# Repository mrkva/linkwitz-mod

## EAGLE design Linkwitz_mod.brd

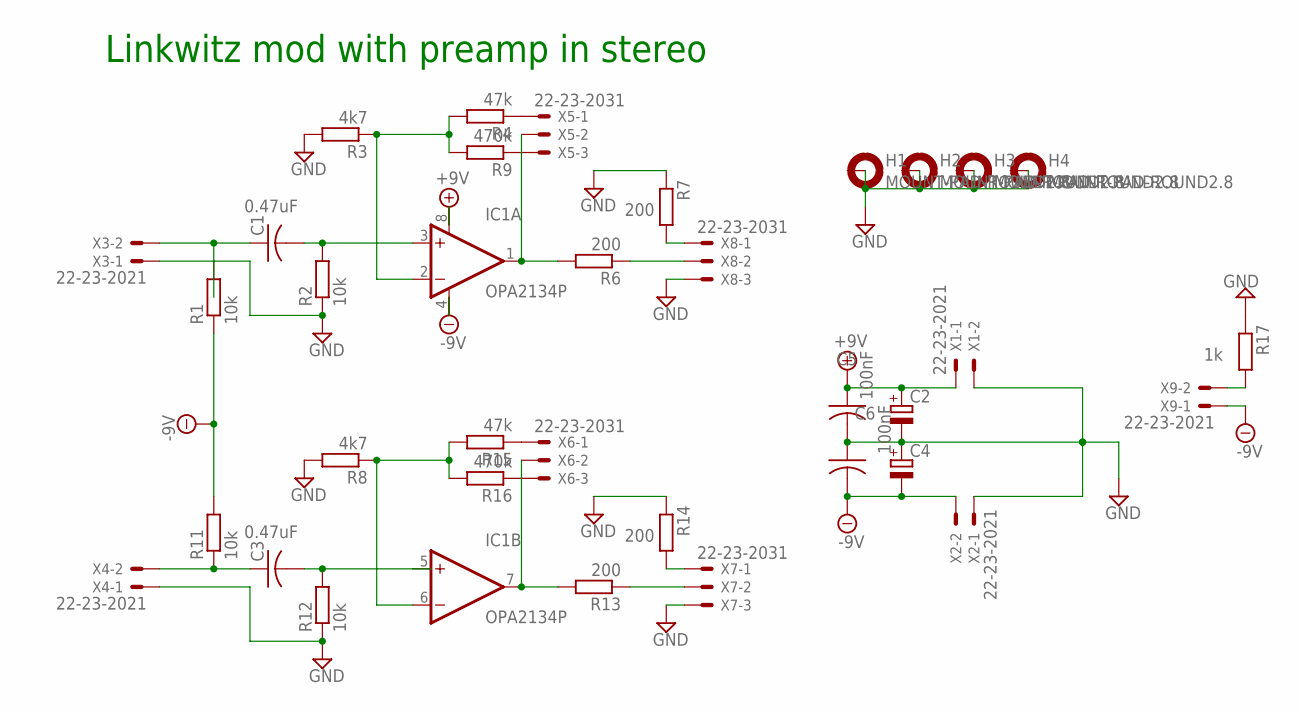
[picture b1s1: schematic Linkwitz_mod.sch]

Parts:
C1, C3: 0.47uF; C050-030X075
C2, C4: CPOL-EUE2,5-6E; E2,5-6E
C5, C6: 100nF; C050-030X075
H1, H2, H3, H4: MOUNT-PAD-ROUND2.8; 2,8-PAD
IC1: OPA2134P; DIL08
R1, R2, R11, R12: 10k; 0309/10
R3, R8: 4k7; 0309/10
R4, R15: 47k; 0309/10
R6, R7, R13, R14: 200; 0309/10
R9, R16: 470k; 0309/10
R17: 1k; 0309/10
X1, X2, X9: 22-23-2021; MPN 22-23-2021
X3, X4: 22-23-2021
X5, X6, X7, X8: 22-23-2031

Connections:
+9V: C2.+, C5.1, IC1.8 (V+), X1.1
-9V: C4.-, C6.2, IC1.4 (V-), R1.1, R11.2, X2.2, X9.1
GND: C2.-, C4.+, C5.2, C6.1, R2.1, R3.2, R7.1, R8.2, R12.1, R14.1, R17.1, X1.2, X2.1, X3.1, X4.1, X7.3, X8.3
unnamed: C1.1, R1.2, X3.2
unnamed: IC1.6 (-IN), R8.1, R15.2, R16.2
unnamed: IC1.2 (-IN), R3.1, R4.2, R9.2
unnamed: C1.2, IC1.3 (+IN), R2.2
unnamed: IC1.1 (OUT), R6.2, X5.2
unnamed: R14.2, X7.1
unnamed: R6.1, X8.2
unnamed: R4.1, X5.1
unnamed: R9.1, X5.3
unnamed: IC1.7 (OUT), R13.2, X6.2
unnamed: R7.2, X8.1
unnamed: C3.1, R11.1, X4.2
unnamed: C3.2, IC1.5 (+IN), R12.2
unnamed: R13.1, X7.2
unnamed: R15.1, X6.1
unnamed: R16.1, X6.3
unnamed: R17.2, X9.2

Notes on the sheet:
Linkwitz mod with preamp in stereo

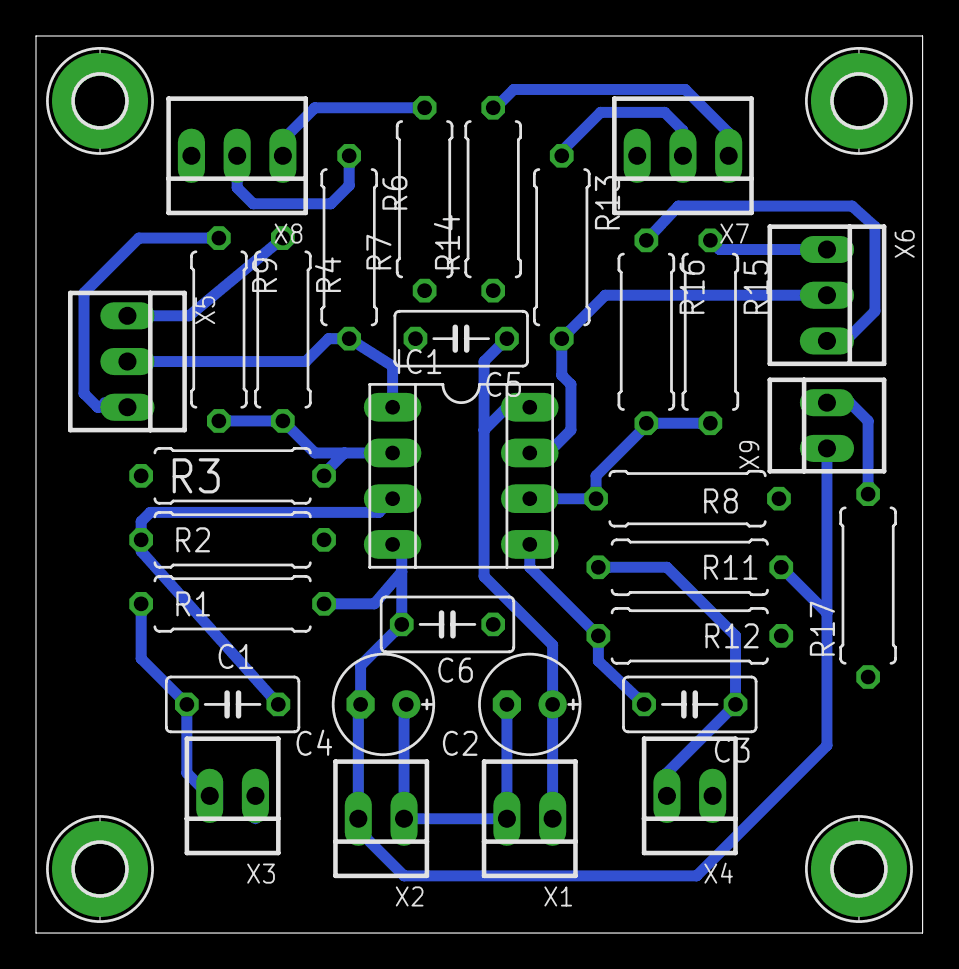
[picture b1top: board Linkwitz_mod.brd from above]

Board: 2 copper layers, 49.3 x 49.8 mm, 35 parts (0 on the bottom side), 20 nets.

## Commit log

2013-03-13 first
